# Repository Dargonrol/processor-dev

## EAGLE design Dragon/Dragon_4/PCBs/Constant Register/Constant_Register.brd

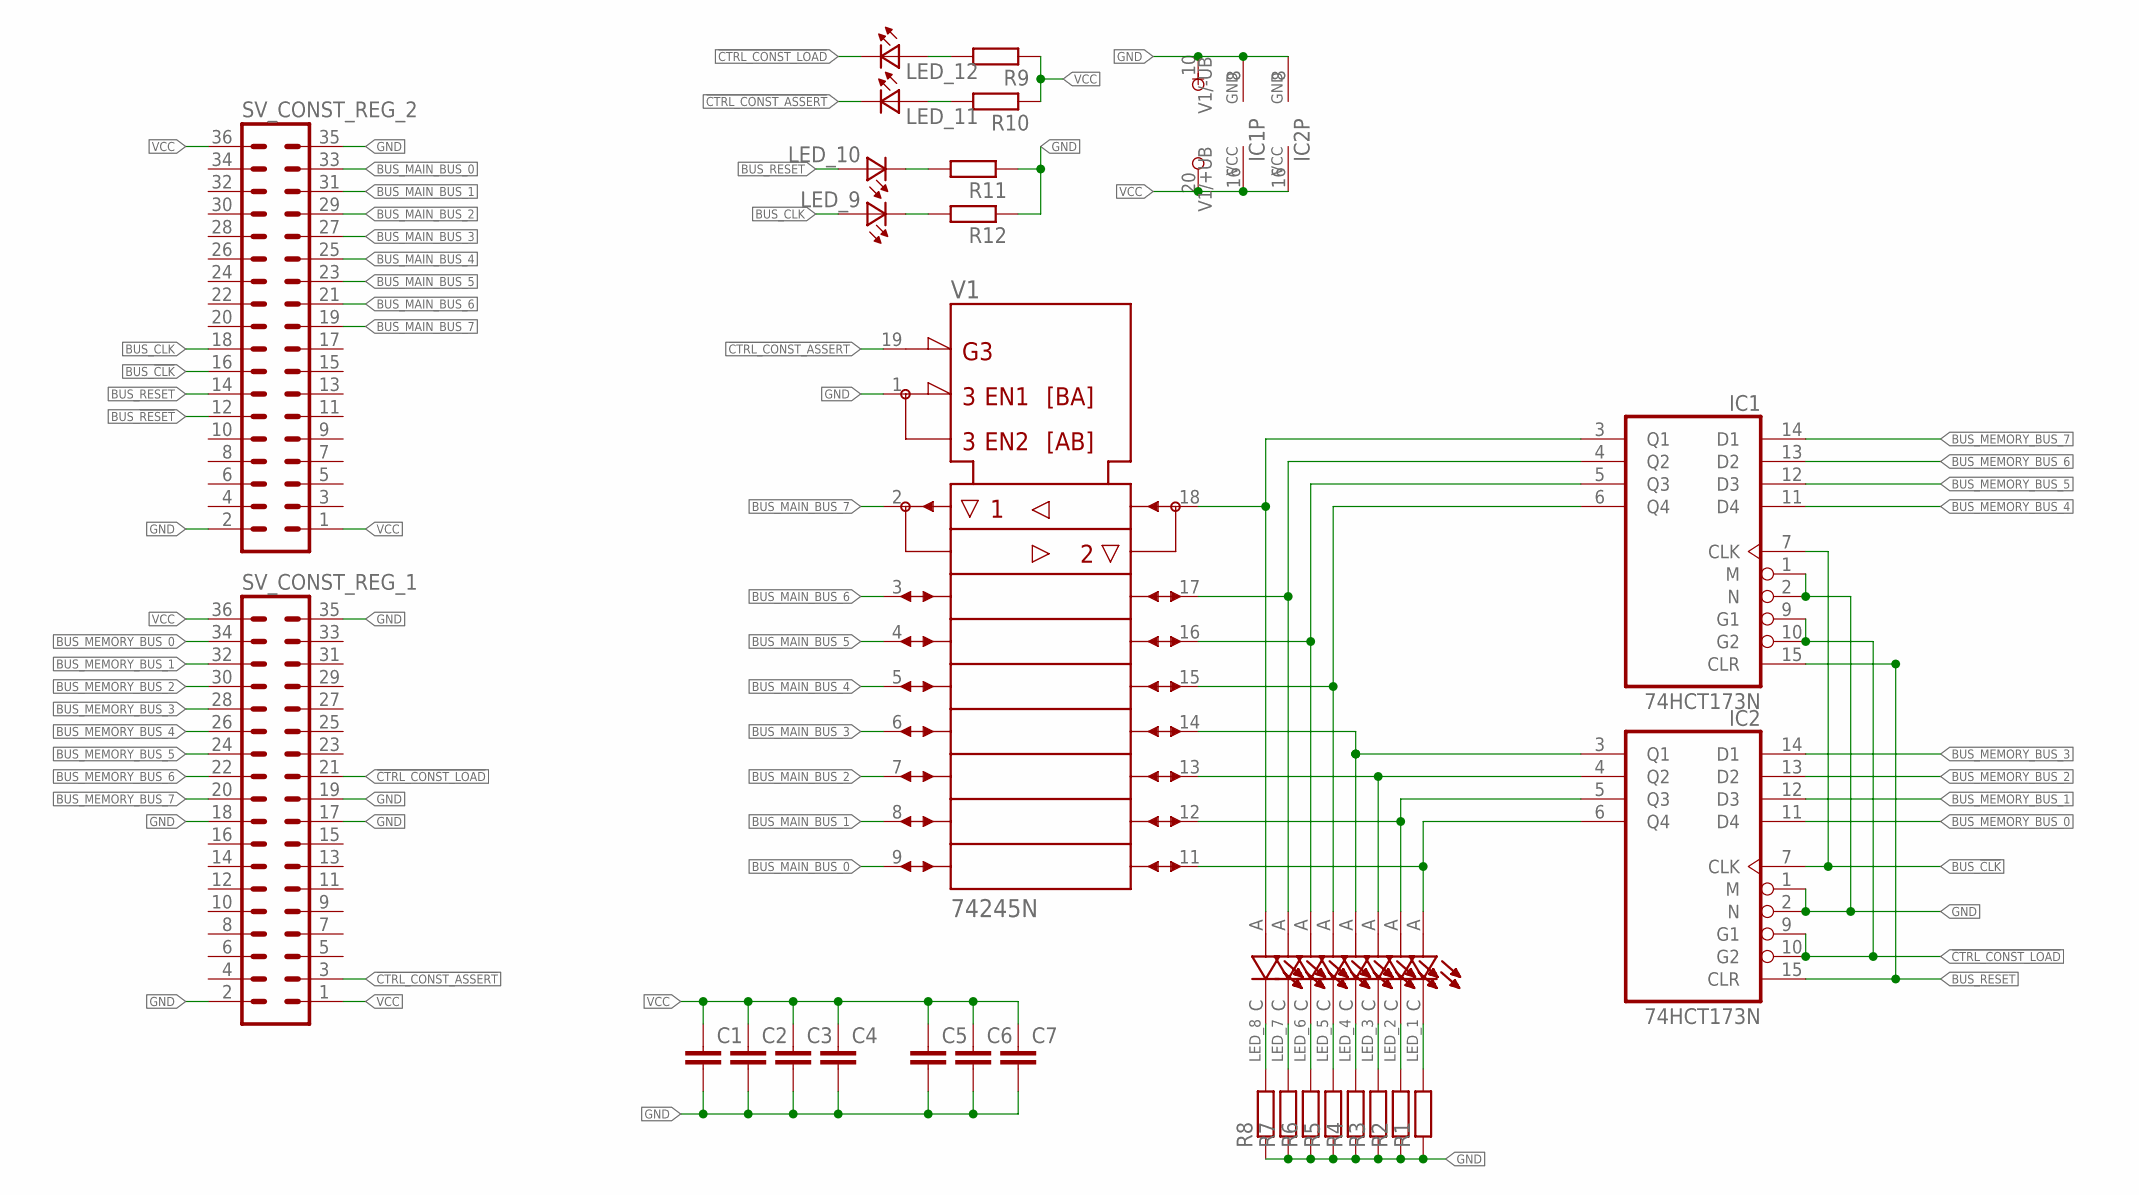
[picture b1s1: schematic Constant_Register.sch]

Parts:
C1, C2, C3, C4, C5, C6, C7: C-EUC0805; C0805
IC1, IC2: 74HCT173N; DIL16
LED_1, LED_2, LED_3, LED_4, LED_5, LED_6, LED_7, LED_8: LTST-C193KRKT-5A; LEDC1608X45N
LED_9, LED_10, LED_11, LED_12: LTST-C193TBKT-5A; 0603
R1, R2, R3, R4, R5, R6, R7, R8, R9, R10, R11, R12: R-EU_R0805; R0805
SV_CONST_REG_1, SV_CONST_REG_2: MA18-2
V1: 74245N; DIL20

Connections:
!CTRL_CONST_ASSERT: LED_11.1 (K2), SV_CONST_REG_1.3, V1.19 (!G)
!CTRL_CONST_LOAD: IC1.9 (G1), IC1.10 (G2), IC2.9 (G1), IC2.10 (G2), LED_12.1 (K2), SV_CONST_REG_1.21
BUS_!CLK: IC1.7 (CLK), IC2.7 (CLK), SV_CONST_REG_2.16
BUS_!RESET: SV_CONST_REG_2.12
BUS_CLK: LED_9.2 (A2), SV_CONST_REG_2.18
BUS_MAIN_BUS_0: SV_CONST_REG_2.33, V1.9 (A8)
BUS_MAIN_BUS_1: SV_CONST_REG_2.31, V1.8 (A7)
BUS_MAIN_BUS_2: SV_CONST_REG_2.29, V1.7 (A6)
BUS_MAIN_BUS_3: SV_CONST_REG_2.27, V1.6 (A5)
BUS_MAIN_BUS_4: SV_CONST_REG_2.25, V1.5 (A4)
BUS_MAIN_BUS_5: SV_CONST_REG_2.23, V1.4 (A3)
BUS_MAIN_BUS_6: SV_CONST_REG_2.21, V1.3 (A2)
BUS_MAIN_BUS_7: SV_CONST_REG_2.19, V1.2 (A1)
BUS_MEMORY_BUS_0: IC2.11 (D4), SV_CONST_REG_1.34
BUS_MEMORY_BUS_1: IC2.12 (D3), SV_CONST_REG_1.32
BUS_MEMORY_BUS_2: IC2.13 (D2), SV_CONST_REG_1.30
BUS_MEMORY_BUS_3: IC2.14 (D1), SV_CONST_REG_1.28
BUS_MEMORY_BUS_4: IC1.11 (D4), SV_CONST_REG_1.26
BUS_MEMORY_BUS_5: IC1.12 (D3), SV_CONST_REG_1.24
BUS_MEMORY_BUS_6: IC1.13 (D2), SV_CONST_REG_1.22
BUS_MEMORY_BUS_7: IC1.14 (D1), SV_CONST_REG_1.20
BUS_RESET: IC1.15 (CLR), IC2.15 (CLR), LED_10.2 (A2), SV_CONST_REG_2.14
GND: C1.2, C2.2, C3.2, C4.2, C5.2, C6.2, C7.2, IC1.1 (M), IC1.2 (N), IC1.8 (GND), IC2.1 (M), IC2.2 (N), IC2.8 (GND), R1.1, R2.1, R3.1, R4.1, R5.1, R6.1, R7.1, R8.1, R11.1, R12.1, SV_CONST_REG_1.2, SV_CONST_REG_1.17, SV_CONST_REG_1.18, SV_CONST_REG_1.19, SV_CONST_REG_1.35, SV_CONST_REG_2.2, SV_CONST_REG_2.35, V1.1 (DIR), V1.10 (-UB)
unnamed: LED_8.C, R8.2
unnamed: LED_7.C, R7.2
unnamed: LED_6.C, R6.2
unnamed: LED_5.C, R5.2
unnamed: LED_4.C, R4.2
unnamed: LED_3.C, R3.2
unnamed: LED_2.C, R2.2
unnamed: LED_1.C, R1.2
unnamed: IC2.3 (Q1), LED_4.A, V1.14 (B5)
unnamed: IC1.4 (Q2), LED_7.A, V1.17 (B2)
unnamed: IC2.6 (Q4), LED_1.A, V1.11 (B8)
unnamed: IC2.5 (Q3), LED_2.A, V1.12 (B7)
unnamed: IC2.4 (Q2), LED_3.A, V1.13 (B6)
unnamed: IC1.6 (Q4), LED_5.A, V1.15 (B4)
unnamed: IC1.5 (Q3), LED_6.A, V1.16 (B3)
unnamed: IC1.3 (Q1), LED_8.A, V1.18 (B1)
unnamed: LED_11.2 (A2), R10.2
unnamed: LED_12.2 (A2), R9.2
unnamed: LED_9.1 (K2), R12.2
unnamed: LED_10.1 (K2), R11.2
VCC: C1.1, C2.1, C3.1, C4.1, C5.1, C6.1, C7.1, IC1.16 (VCC), IC2.16 (VCC), R9.1, R10.1, SV_CONST_REG_1.1, SV_CONST_REG_1.36, SV_CONST_REG_2.1, SV_CONST_REG_2.36, V1.20 (+UB)

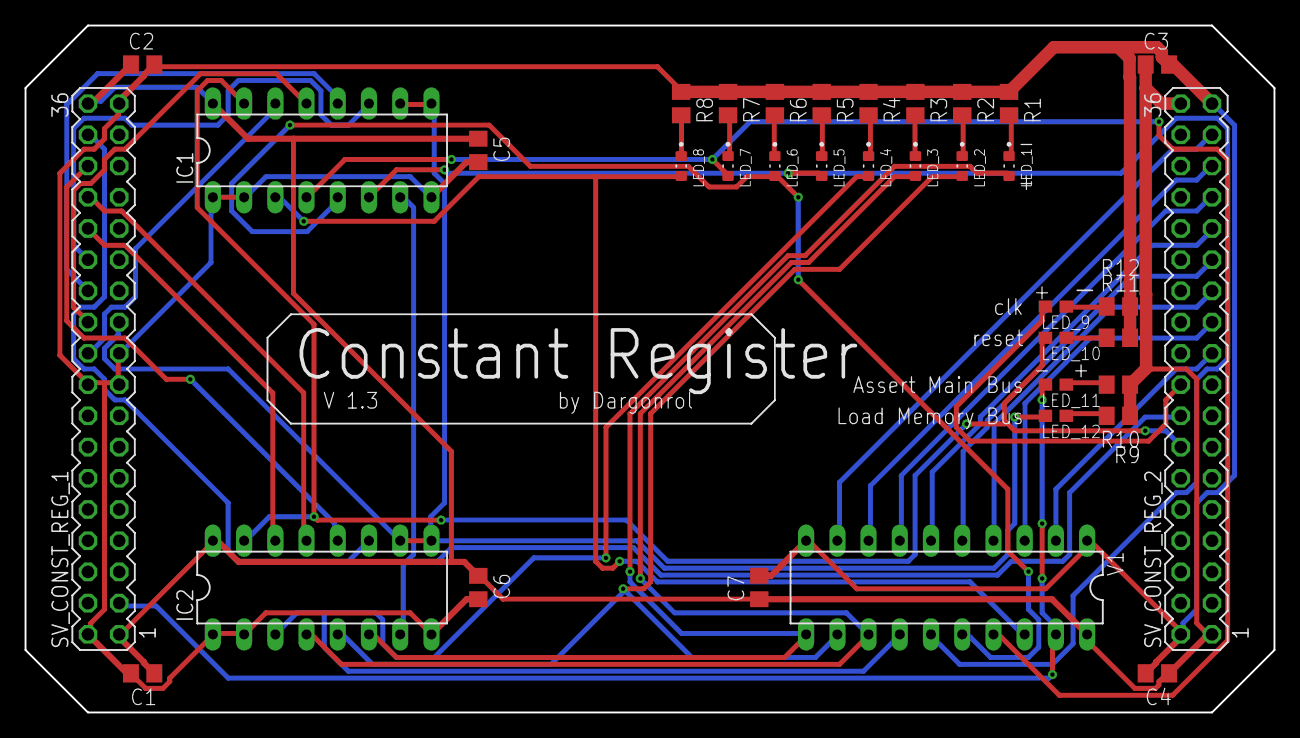
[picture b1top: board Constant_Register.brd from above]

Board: 2 copper layers, 101.6 x 55.9 mm, 36 parts (0 on the bottom side), 43 nets.

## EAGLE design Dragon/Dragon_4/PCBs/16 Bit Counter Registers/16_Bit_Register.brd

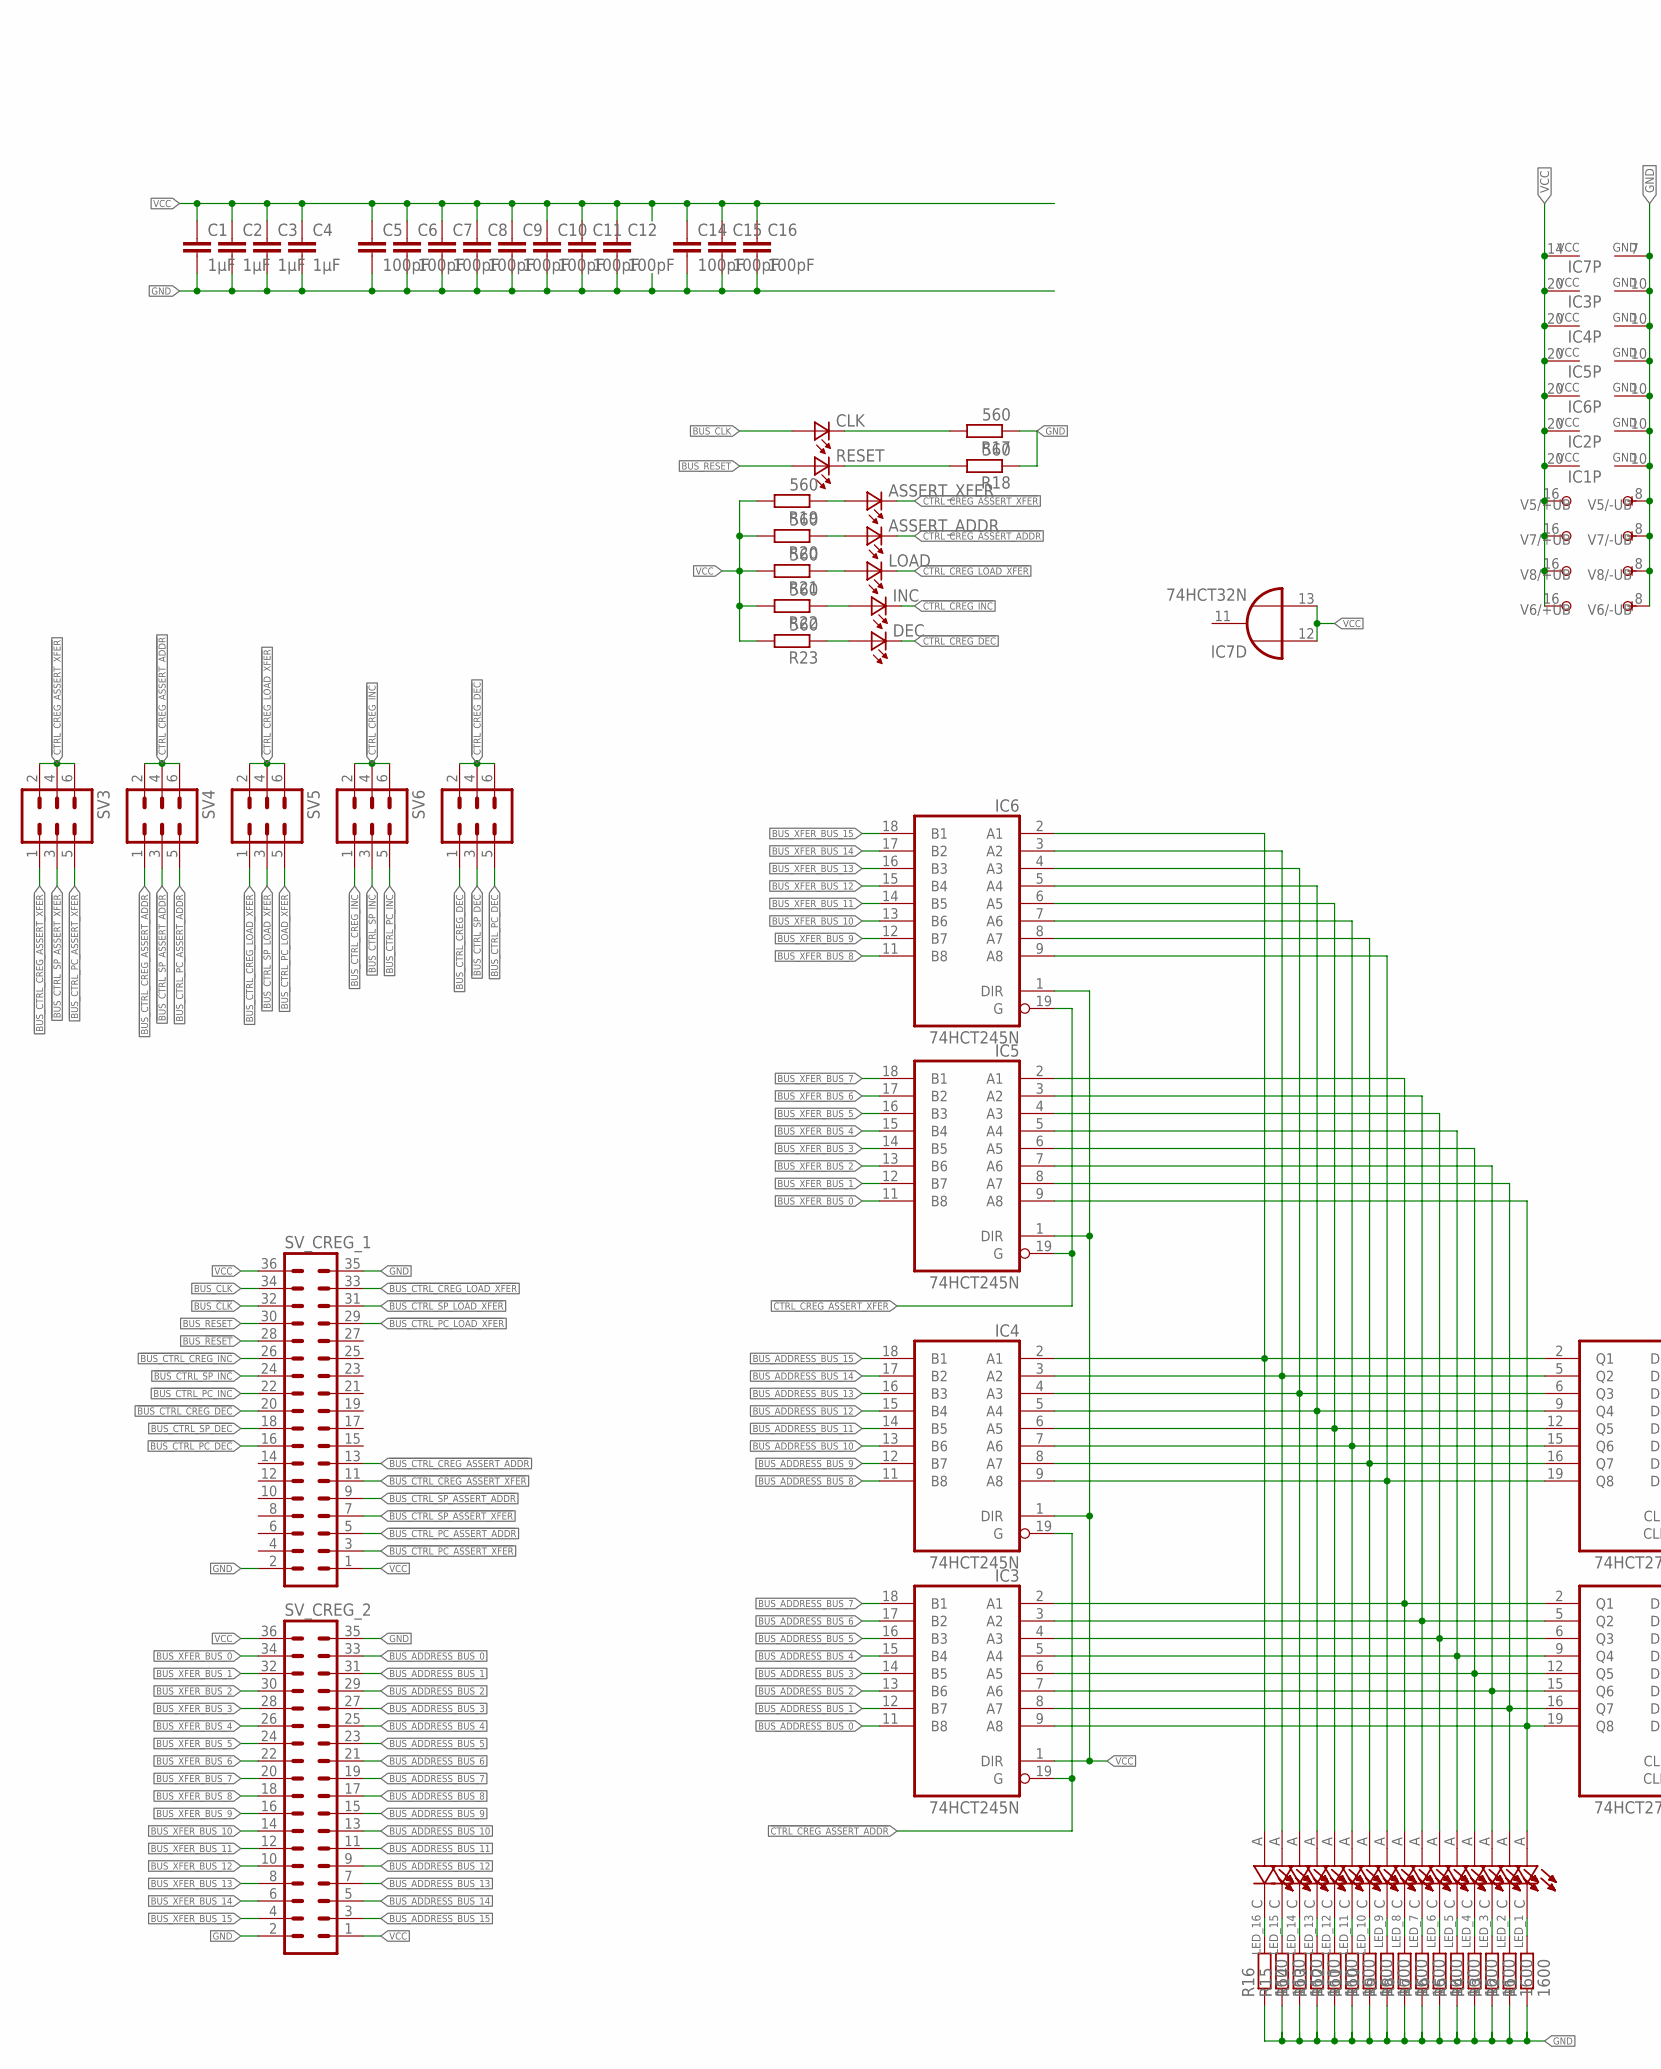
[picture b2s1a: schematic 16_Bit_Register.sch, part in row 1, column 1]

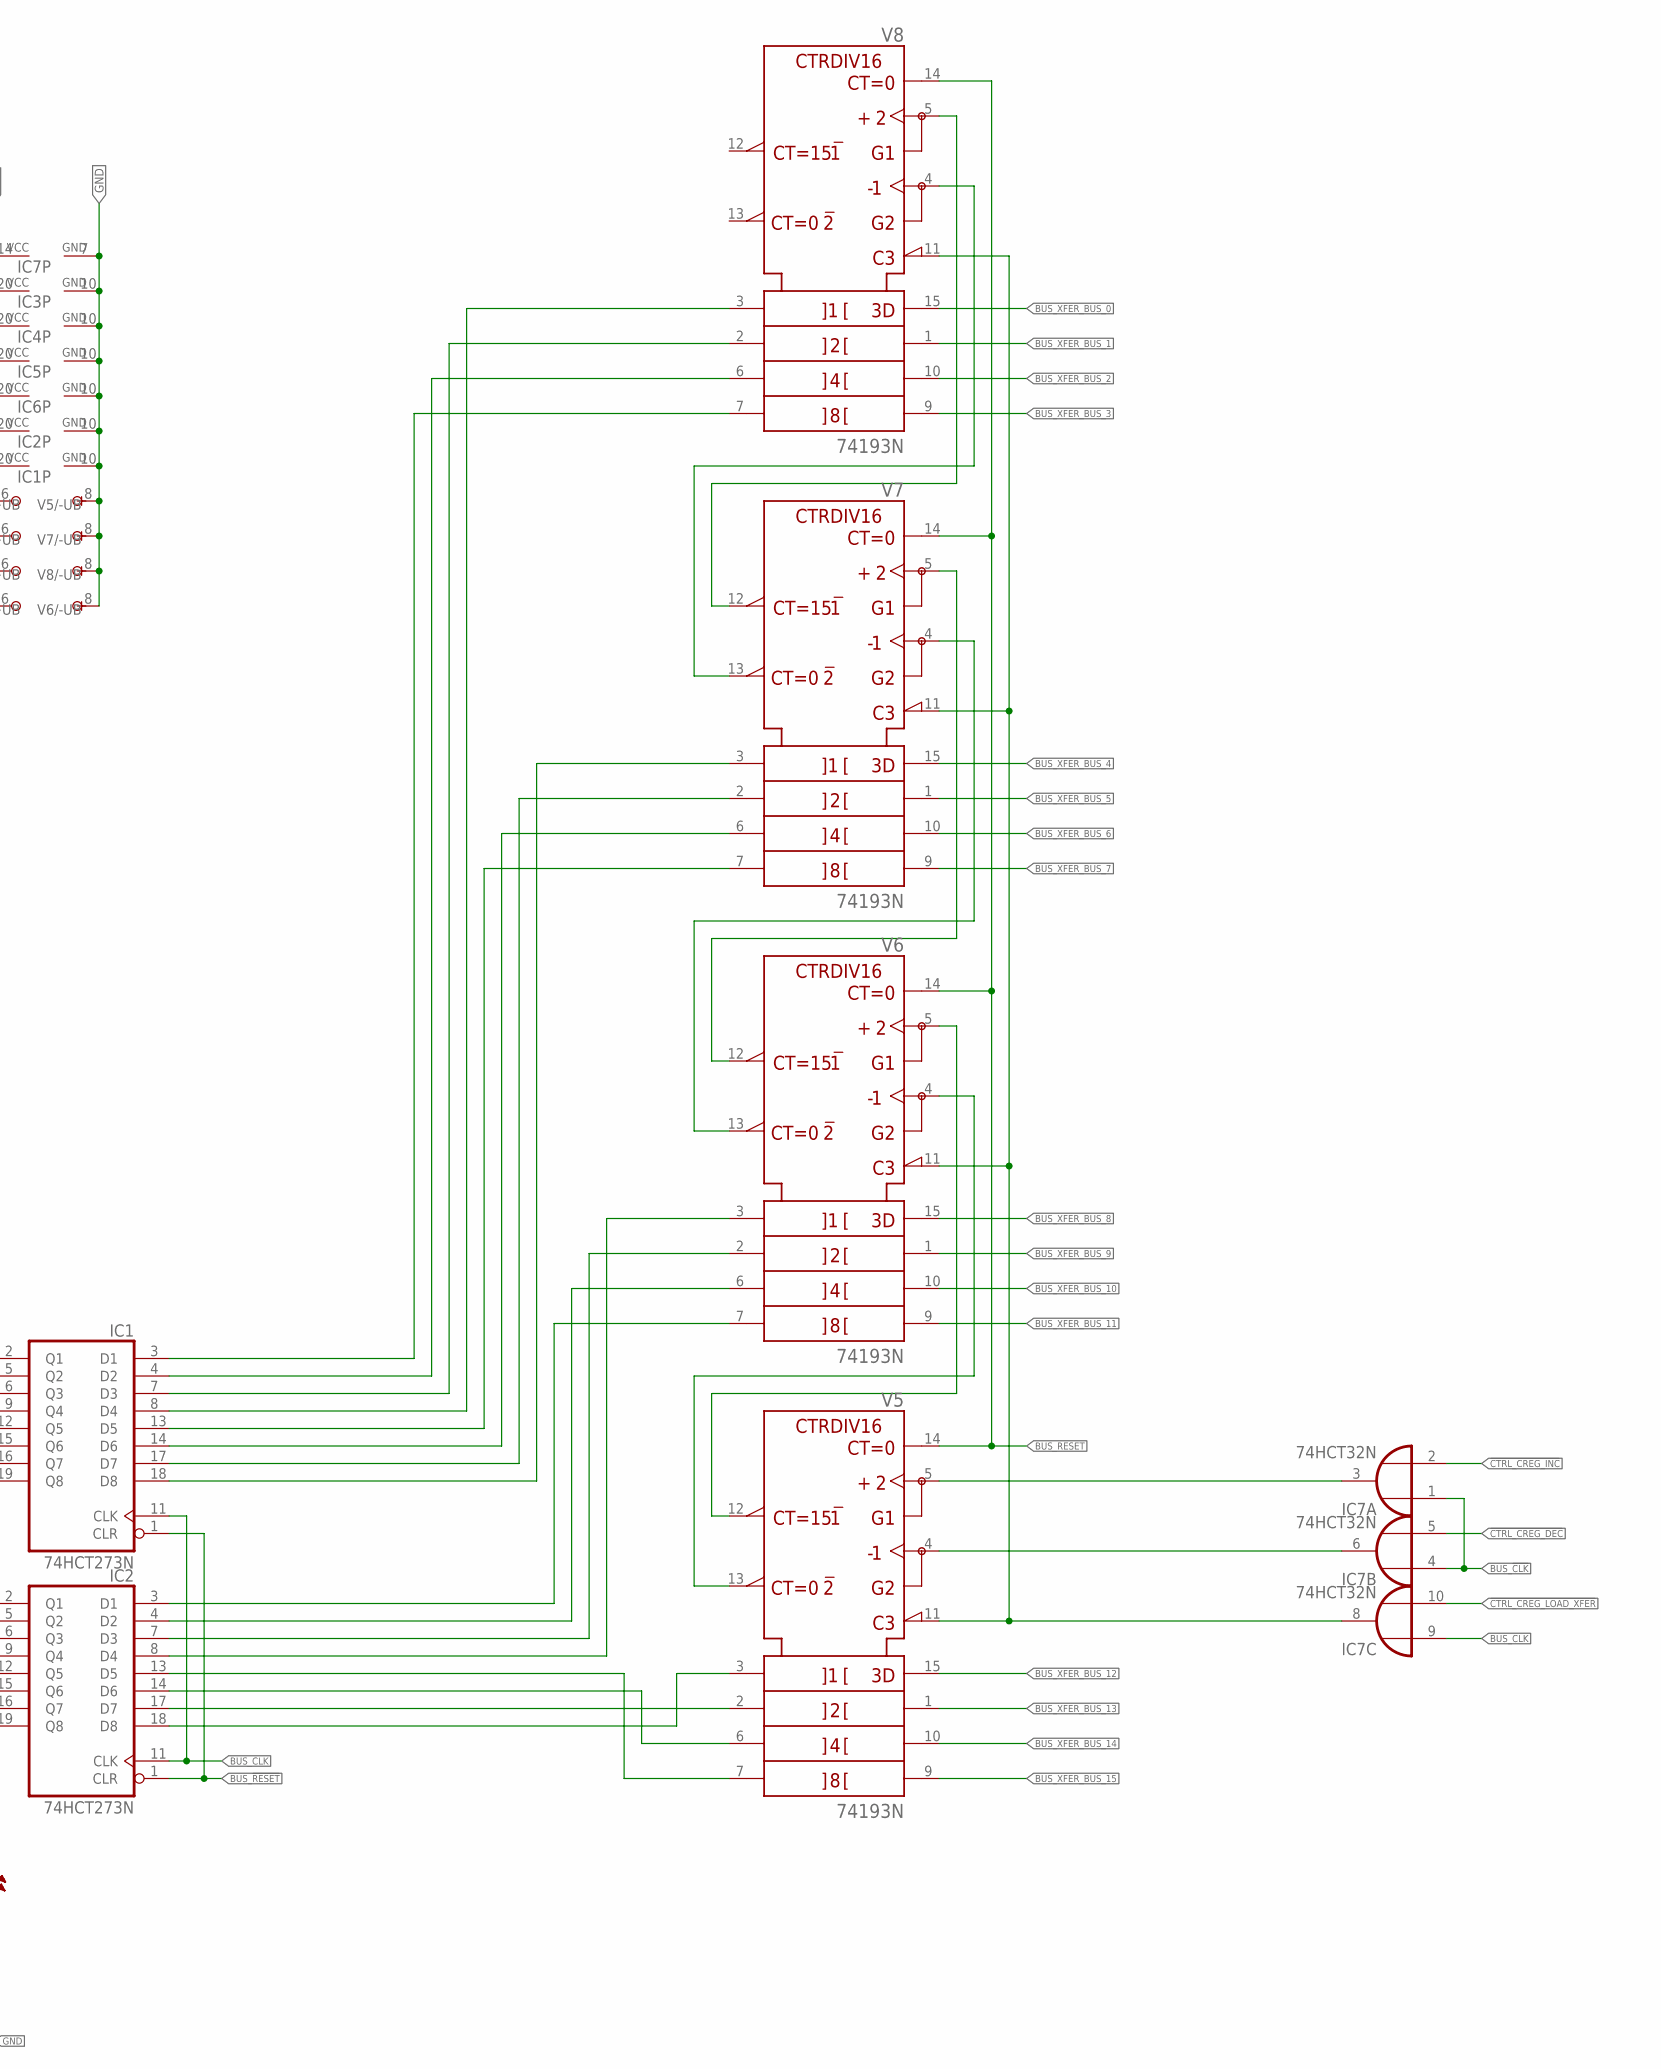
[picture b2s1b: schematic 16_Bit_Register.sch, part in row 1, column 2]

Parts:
ASSERT_ADDR: LTST-C193TBKT-5A; 0603
ASSERT_XFER: LTST-C193TBKT-5A; 0603
C1, C2, C3, C4: 1µF; C0805
C5, C6, C7, C8, C9, C10, C11, C12, C14, C15, C16: 100pF; C0805
CLK: LTST-C193TBKT-5A; 0603
DEC: LTST-C193TBKT-5A; 0603
IC1, IC2: 74HCT273N; DIL20
IC3, IC4, IC5, IC6: 74HCT245N; DIL20
IC7: 74HCT32N; DIL14
INC: LTST-C193TBKT-5A; 0603
LED_1, LED_2, LED_3, LED_4, LED_5, LED_6, LED_7, LED_8, LED_9, LED_10, LED_11, LED_12, LED_13, LED_14, LED_15, LED_16: LTST-C193KRKT-5A; LEDC1608X45N
LOAD: LTST-C193TBKT-5A; 0603
R1, R2, R3, R4, R5, R6, R7, R8, R9, R10, R11, R12, R13, R14, R15, R16: 1600; R0805
R17, R18, R19, R20, R21, R22, R23: 560; R0805
RESET: LTST-C193TBKT-5A; 0603
SV3, SV4, SV5, SV6, SV7: MA03-2
SV_CREG_1, SV_CREG_2: MA18-2
V5, V6, V7, V8: 74193N; DIL16

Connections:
!BUS_CTRL_CREG_ASSERT_ADDR: SV4.1, SV_CREG_1.13
!BUS_CTRL_CREG_ASSERT_XFER: SV3.1, SV_CREG_1.11
!BUS_CTRL_CREG_DEC: SV7.1, SV_CREG_1.20
!BUS_CTRL_CREG_INC: SV6.1, SV_CREG_1.26
!BUS_CTRL_CREG_LOAD_XFER: SV5.1, SV_CREG_1.33
!BUS_CTRL_PC_ASSERT_ADDR: SV4.5, SV_CREG_1.5
!BUS_CTRL_PC_ASSERT_XFER: SV3.5, SV_CREG_1.3
!BUS_CTRL_PC_DEC: SV7.5, SV_CREG_1.16
!BUS_CTRL_PC_INC: SV6.5, SV_CREG_1.22
!BUS_CTRL_PC_LOAD_XFER: SV5.5, SV_CREG_1.29
!BUS_CTRL_SP_ASSERT_ADDR: SV4.3, SV_CREG_1.9
!BUS_CTRL_SP_ASSERT_XFER: SV3.3, SV_CREG_1.7
!BUS_CTRL_SP_DEC: SV7.3, SV_CREG_1.18
!BUS_CTRL_SP_INC: SV6.3, SV_CREG_1.24
!BUS_CTRL_SP_LOAD_XFER: SV5.3, SV_CREG_1.31
!CTRL_CREG_ASSERT_ADDR: ASSERT_ADDR.1 (K2), IC3.19 (G), IC4.19 (G), SV4.2, SV4.4, SV4.6
!CTRL_CREG_ASSERT_XFER: ASSERT_XFER.1 (K2), IC5.19 (G), IC6.19 (G), SV3.2, SV3.4, SV3.6
!CTRL_CREG_DEC: DEC.1 (K2), IC7.5 (I1), SV7.2, SV7.4, SV7.6
!CTRL_CREG_INC: IC7.2 (I1), INC.1 (K2), SV6.2, SV6.4, SV6.6
!CTRL_CREG_LOAD_XFER: IC7.10 (I1), LOAD.1 (K2), SV5.2, SV5.4, SV5.6
BUS_!CLK: IC7.1 (I0), IC7.4 (I0), SV_CREG_1.32
BUS_!RESET: IC1.1 (CLR), IC2.1 (CLR), SV_CREG_1.28
BUS_ADDRESS_BUS_0: IC3.11 (B8), SV_CREG_2.33
BUS_ADDRESS_BUS_1: IC3.12 (B7), SV_CREG_2.31
BUS_ADDRESS_BUS_2: IC3.13 (B6), SV_CREG_2.29
BUS_ADDRESS_BUS_3: IC3.14 (B5), SV_CREG_2.27
BUS_ADDRESS_BUS_4: IC3.15 (B4), SV_CREG_2.25
BUS_ADDRESS_BUS_5: IC3.16 (B3), SV_CREG_2.23
BUS_ADDRESS_BUS_6: IC3.17 (B2), SV_CREG_2.21
BUS_ADDRESS_BUS_7: IC3.18 (B1), SV_CREG_2.19
BUS_ADDRESS_BUS_8: IC4.11 (B8), SV_CREG_2.17
BUS_ADDRESS_BUS_9: IC4.12 (B7), SV_CREG_2.15
BUS_ADDRESS_BUS_10: IC4.13 (B6), SV_CREG_2.13
BUS_ADDRESS_BUS_11: IC4.14 (B5), SV_CREG_2.11
BUS_ADDRESS_BUS_12: IC4.15 (B4), SV_CREG_2.9
BUS_ADDRESS_BUS_13: IC4.16 (B3), SV_CREG_2.7
BUS_ADDRESS_BUS_14: IC4.17 (B2), SV_CREG_2.5
BUS_ADDRESS_BUS_15: IC4.18 (B1), SV_CREG_2.3
BUS_CLK: CLK.2 (A2), IC1.11 (CLK), IC2.11 (CLK), IC7.9 (I0), SV_CREG_1.34
BUS_RESET: RESET.2 (A2), SV_CREG_1.30, V5.14 (CLR), V6.14 (CLR), V7.14 (CLR), V8.14 (CLR)
BUS_XFER_BUS_0: IC5.11 (B8), SV_CREG_2.34, V8.15 (A)
BUS_XFER_BUS_1: IC5.12 (B7), SV_CREG_2.32, V8.1 (B)
BUS_XFER_BUS_2: IC5.13 (B6), SV_CREG_2.30, V8.10 (C)
BUS_XFER_BUS_3: IC5.14 (B5), SV_CREG_2.28, V8.9 (D)
BUS_XFER_BUS_4: IC5.15 (B4), SV_CREG_2.26, V7.15 (A)
BUS_XFER_BUS_5: IC5.16 (B3), SV_CREG_2.24, V7.1 (B)
BUS_XFER_BUS_6: IC5.17 (B2), SV_CREG_2.22, V7.10 (C)
BUS_XFER_BUS_7: IC5.18 (B1), SV_CREG_2.20, V7.9 (D)
BUS_XFER_BUS_8: IC6.11 (B8), SV_CREG_2.18, V6.15 (A)
BUS_XFER_BUS_9: IC6.12 (B7), SV_CREG_2.16, V6.1 (B)
BUS_XFER_BUS_10: IC6.13 (B6), SV_CREG_2.14, V6.10 (C)
BUS_XFER_BUS_11: IC6.14 (B5), SV_CREG_2.12, V6.9 (D)
BUS_XFER_BUS_12: IC6.15 (B4), SV_CREG_2.10, V5.15 (A)
BUS_XFER_BUS_13: IC6.16 (B3), SV_CREG_2.8, V5.1 (B)
BUS_XFER_BUS_14: IC6.17 (B2), SV_CREG_2.6, V5.10 (C)
BUS_XFER_BUS_15: IC6.18 (B1), SV_CREG_2.4, V5.9 (D)
GND: C1.2, C2.2, C3.2, C4.2, C5.2, C6.2, C7.2, C8.2, C9.2, C10.2, C11.2, C12.2, C14.2, C15.2, C16.2, IC1.10 (GND), IC2.10 (GND), IC3.10 (GND), IC4.10 (GND), IC5.10 (GND), IC6.10 (GND), IC7.7 (GND), R1.1, R2.1, R3.1, R4.1, R5.1, R6.1, R7.1, R8.1, R9.1, R10.1, R11.1, R12.1, R13.1, R14.1, R15.1, R16.1, R17.1, R18.1, SV_CREG_1.2, SV_CREG_1.35, SV_CREG_2.2, SV_CREG_2.35, V5.8 (-UB), V6.8 (-UB), V7.8 (-UB), V8.8 (-UB)
unnamed: IC2.19 (Q8), IC3.9 (A8), IC5.9 (A8), LED_1.A
unnamed: IC2.16 (Q7), IC3.8 (A7), IC5.8 (A7), LED_2.A
unnamed: IC2.15 (Q6), IC3.7 (A6), IC5.7 (A6), LED_3.A
unnamed: IC2.12 (Q5), IC3.6 (A5), IC5.6 (A5), LED_4.A
unnamed: IC2.9 (Q4), IC3.5 (A4), IC5.5 (A4), LED_5.A
unnamed: IC2.6 (Q3), IC3.4 (A3), IC5.4 (A3), LED_6.A
unnamed: IC2.5 (Q2), IC3.3 (A2), IC5.3 (A2), LED_7.A
unnamed: IC2.2 (Q1), IC3.2 (A1), IC5.2 (A1), LED_8.A
unnamed: IC1.19 (Q8), IC4.9 (A8), IC6.9 (A8), LED_9.A
unnamed: IC1.16 (Q7), IC4.8 (A7), IC6.8 (A7), LED_10.A
unnamed: IC1.15 (Q6), IC4.7 (A6), IC6.7 (A6), LED_11.A
unnamed: IC1.12 (Q5), IC4.6 (A5), IC6.6 (A5), LED_12.A
unnamed: IC1.9 (Q4), IC4.5 (A4), IC6.5 (A4), LED_13.A
unnamed: IC1.6 (Q3), IC4.4 (A3), IC6.4 (A3), LED_14.A
unnamed: IC1.5 (Q2), IC4.3 (A2), IC6.3 (A2), LED_15.A
unnamed: IC1.2 (Q1), IC4.2 (A1), IC6.2 (A1), LED_16.A
unnamed: LOAD.2 (A2), R21.1
unnamed: ASSERT_ADDR.2 (A2), R20.1
unnamed: LED_1.C, R1.2
unnamed: ASSERT_XFER.2 (A2), R19.1
unnamed: IC2.18 (D8), V5.3 (QA)
unnamed: IC2.17 (D7), V5.2 (QB)
unnamed: IC2.14 (D6), V5.6 (QC)
unnamed: IC2.13 (D5), V5.7 (QD)
unnamed: IC2.8 (D4), V6.3 (QA)
unnamed: IC2.7 (D3), V6.2 (QB)
unnamed: IC2.4 (D2), V6.6 (QC)
unnamed: IC2.3 (D1), V6.7 (QD)
unnamed: IC1.18 (D8), V7.3 (QA)
unnamed: IC1.17 (D7), V7.2 (QB)
unnamed: IC1.14 (D6), V7.6 (QC)
unnamed: IC1.13 (D5), V7.7 (QD)
unnamed: IC1.8 (D4), V8.3 (QA)
unnamed: IC1.7 (D3), V8.2 (QB)
unnamed: IC1.4 (D2), V8.6 (QC)
unnamed: IC1.3 (D1), V8.7 (QD)
unnamed: V5.12 (!CO), V6.5 (UP)
unnamed: V5.13 (!BO), V6.4 (DOWN)
unnamed: V6.12 (!CO), V7.5 (UP)
unnamed: V6.13 (!BO), V7.4 (DOWN)
unnamed: V7.12 (!CO), V8.5 (UP)
unnamed: V7.13 (!BO), V8.4 (DOWN)
unnamed: IC7.6 (O), V5.4 (DOWN)
unnamed: IC7.8 (O), V5.11 (!LOAD), V6.11 (!LOAD), V7.11 (!LOAD), V8.11 (!LOAD)
unnamed: IC7.3 (O), V5.5 (UP)
unnamed: DEC.2 (A2), R23.1
unnamed: INC.2 (A2), R22.1
unnamed: LED_2.C, R2.2
unnamed: LED_3.C, R3.2
unnamed: LED_4.C, R4.2
unnamed: LED_5.C, R5.2
unnamed: LED_6.C, R6.2
unnamed: LED_7.C, R7.2
unnamed: LED_8.C, R8.2
unnamed: LED_9.C, R9.2
unnamed: LED_10.C, R10.2
unnamed: LED_11.C, R11.2
unnamed: LED_12.C, R12.2
unnamed: LED_13.C, R13.2
unnamed: LED_14.C, R14.2
unnamed: CLK.1 (K2), R17.2
unnamed: R18.2, RESET.1 (K2)
unnamed: LED_15.C, R15.2
unnamed: LED_16.C, R16.2
VCC: C1.1, C2.1, C3.1, C4.1, C5.1, C6.1, C7.1, C8.1, C9.1, C10.1, C11.1, C12.1, C14.1, C15.1, C16.1, IC1.20 (VCC), IC2.20 (VCC), IC3.1 (DIR), IC3.20 (VCC), IC4.1 (DIR), IC4.20 (VCC), IC5.1 (DIR), IC5.20 (VCC), IC6.1 (DIR), IC6.20 (VCC), IC7.12 (I0), IC7.13 (I1), IC7.14 (VCC), R19.2, R20.2, R21.2, R22.2, R23.2, SV_CREG_1.1, SV_CREG_1.36, SV_CREG_2.1, SV_CREG_2.36, V5.16 (+UB), V6.16 (+UB), V7.16 (+UB), V8.16 (+UB)

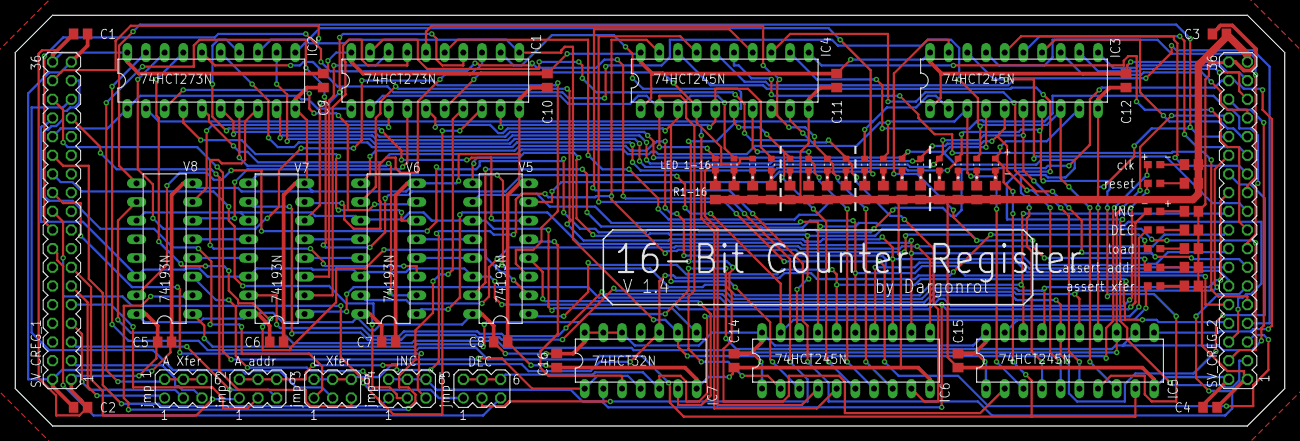
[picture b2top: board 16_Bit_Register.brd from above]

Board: 2 copper layers, 172.7 x 55.9 mm, 79 parts (0 on the bottom side), 122 nets.
